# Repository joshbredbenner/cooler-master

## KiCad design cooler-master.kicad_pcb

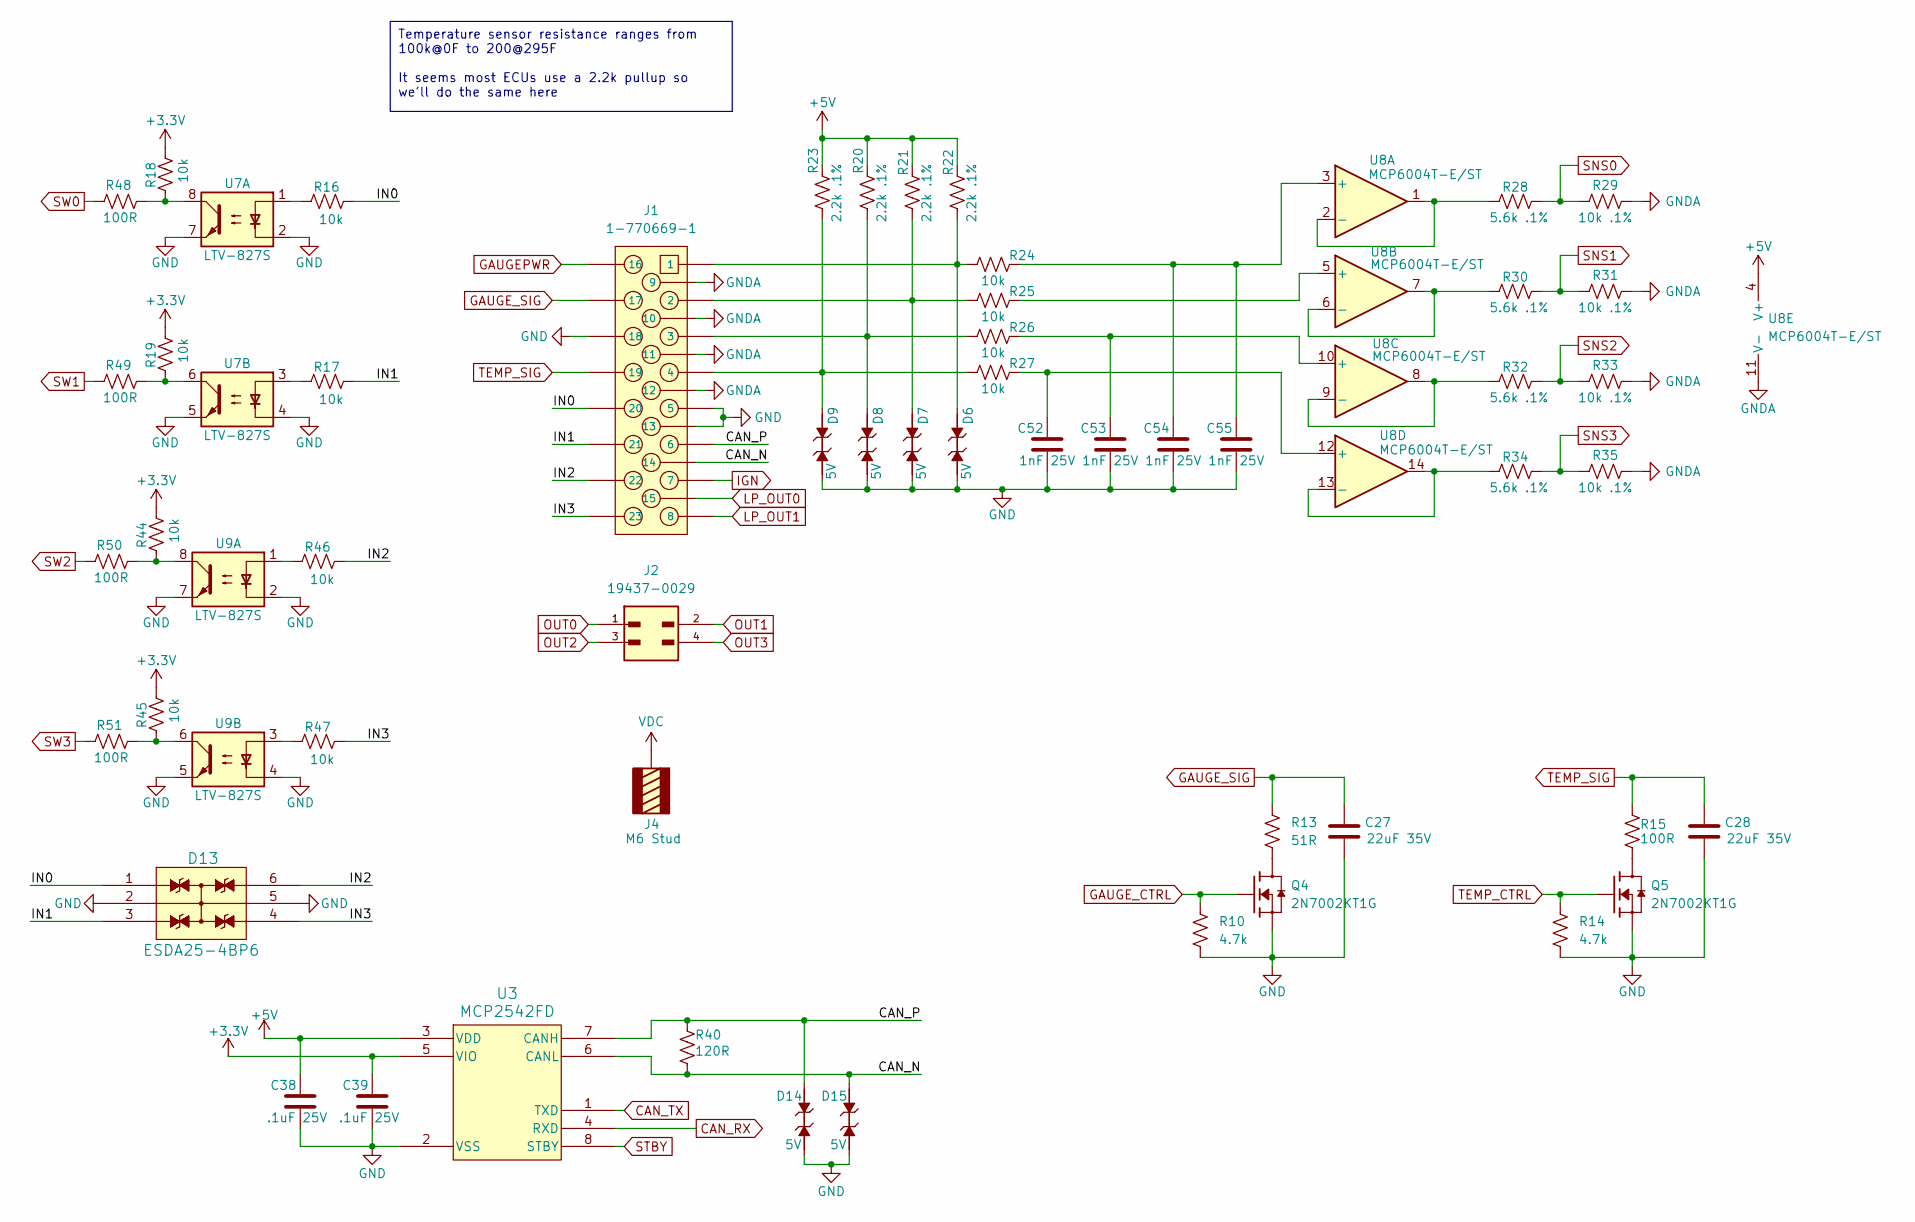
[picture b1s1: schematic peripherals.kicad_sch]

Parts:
C27, C28: 22uF 35V; C_0805_2012Metric
C38, C39: .1uF 25V; C_0402_1005Metric
C52, C53, C54, C55: 1nF 25V; C_0402_1005Metric
D6, D7, D8, D9, D14, D15: 5V; ESD9B5.0ST5G
D13: ESDA25-4BP6; SOT666_ESDA25_STM
J1: 1-770669-1; 17706691
J2: 19437-0029; MOLEX_19437-0029; PARTREV A
J4: M6 Stud; WP-BUCF_7461059
Q4, Q5: 2N7002KT1G; SOT95P230X110-3N
R10, R14: 4.7k; R_0402_1005Metric
R13: 51R; R_0805_2012Metric
R15: 100R; R_0805_2012Metric
R16, R17, R18, R19, R24, R25, R26, R27, R44, R45, R46, R47: 10k; R_0402_1005Metric
R20, R21, R22, R23: 2.2k .1%; R_0402_1005Metric
R28, R30, R32, R34: 5.6k .1%; R_0402_1005Metric
R29, R31, R33, R35: 10k .1%; R_0402_1005Metric
R40: 120R; R_0603_1608Metric
R48, R49, R50, R51: 100R; R_0402_1005Metric
U3: MCP2542FD; SOIC8_4P9X3P9MC_MCH
U7, U9: LTV-827S; SMDIP-8_W9.53mm
U8: MCP6004T-E/ST; SOP65P640X120-14N

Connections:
+3.3V: C39.1, R18.1, R19.1, R44.1, R45.1, U3.5 (VIO); also elsewhere on the board
+5V: C38.1, R20.1, R21.1, R22.1, R23.1, U3.3 (VDD), U8.4 (V+); also elsewhere on the board
/Peripherals/CAN_N: D15.2, J1.14, R40.2, U3.6 (CANL)
/Peripherals/CAN_P: D14.2, J1.6, R40.1, U3.7 (CANH)
/Peripherals/IN0: D13.1, J1.20, R16.1
/Peripherals/IN1: D13.3, J1.21, R17.1
/Peripherals/IN2: D13.6, J1.22, R46.1
/Peripherals/IN3: D13.4, J1.23, R47.1
CAN_RX: U3.4 (RXD); also elsewhere on the board
CAN_TX: U3.1 (TXD); also elsewhere on the board
GAUGEPWR: J1.16; also elsewhere on the board
GAUGE_CTRL: Q4.1 (G), R10.1; also elsewhere on the board
GAUGE_SIG: C27.1, J1.17, R13.1
GND: C27.2, C28.2, C38.2, C39.2, C52.2, C53.2, C54.2, C55.2, D6.2, D7.2, D8.2, D9.2, D13.2, D13.5, D14.1, D15.1, J1.5, J1.13, J1.18, Q4.2 (S), Q5.2 (S), R10.2, R14.2, U3.2 (VSS), U7.2, U7.4, U7.5, U7.7, U9.2, U9.4, U9.5, U9.7; also elsewhere on the board
GNDA: J1.9, J1.10, J1.11, J1.12, R29.2, R31.2, R33.2, R35.2, U8.11 (V-); also elsewhere on the board
IGN: J1.7; also elsewhere on the board
LP_OUT0: J1.15; also elsewhere on the board
LP_OUT1: J1.8; also elsewhere on the board
unnamed: D6.1, J1.1, R22.2, R24.1
unnamed: D7.1, J1.2, R21.2, R25.1
unnamed: D8.1, J1.3, R20.2, R26.1
unnamed: D9.1, J1.4, R23.2, R27.1
unnamed: Q4.3 (D), R13.2
unnamed: Q5.3 (D), R15.2
unnamed: R16.2, U7.1
unnamed: R17.2, U7.3
unnamed: R18.2, R48.2, U7.8
unnamed: R19.2, R49.2, U7.6
unnamed: R44.2, R50.2, U9.8
unnamed: R45.2, R51.2, U9.6
unnamed: R46.2, U9.1
unnamed: R47.2, U9.3
unnamed: C54.1, C55.1, R24.2, U8.3 (+)
unnamed: R28.2, U8.1, U8.2 (-)
unnamed: R25.2, U8.5 (+)
unnamed: R30.2, U8.6 (-), U8.7
unnamed: C53.1, R26.2, U8.10 (+)
unnamed: R32.2, U8.8, U8.9 (-)
unnamed: C52.1, R27.2, U8.12 (+)
unnamed: R34.2, U8.13 (-), U8.14
OUT0: J2.1; also elsewhere on the board
OUT1: J2.2; also elsewhere on the board
OUT2: J2.3; also elsewhere on the board
OUT3: J2.4; also elsewhere on the board
SNS0: R28.1, R29.1; also elsewhere on the board
SNS1: R30.1, R31.1; also elsewhere on the board
SNS2: R32.1, R33.1; also elsewhere on the board
SNS3: R34.1, R35.1; also elsewhere on the board
STBY: U3.8 (STBY); also elsewhere on the board
SW0: R48.1
SW1: R49.1
SW2: R50.1
SW3: R51.1
TEMP_CTRL: Q5.1 (G), R14.1; also elsewhere on the board
TEMP_SIG: C28.1, J1.19, R15.1
VDC: J4.1; also elsewhere on the board

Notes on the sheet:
Temperature sensor resistance ranges from 100k@0F to 200@295F It seems most ECUs use a 2.2k pullup so we'll do the same here

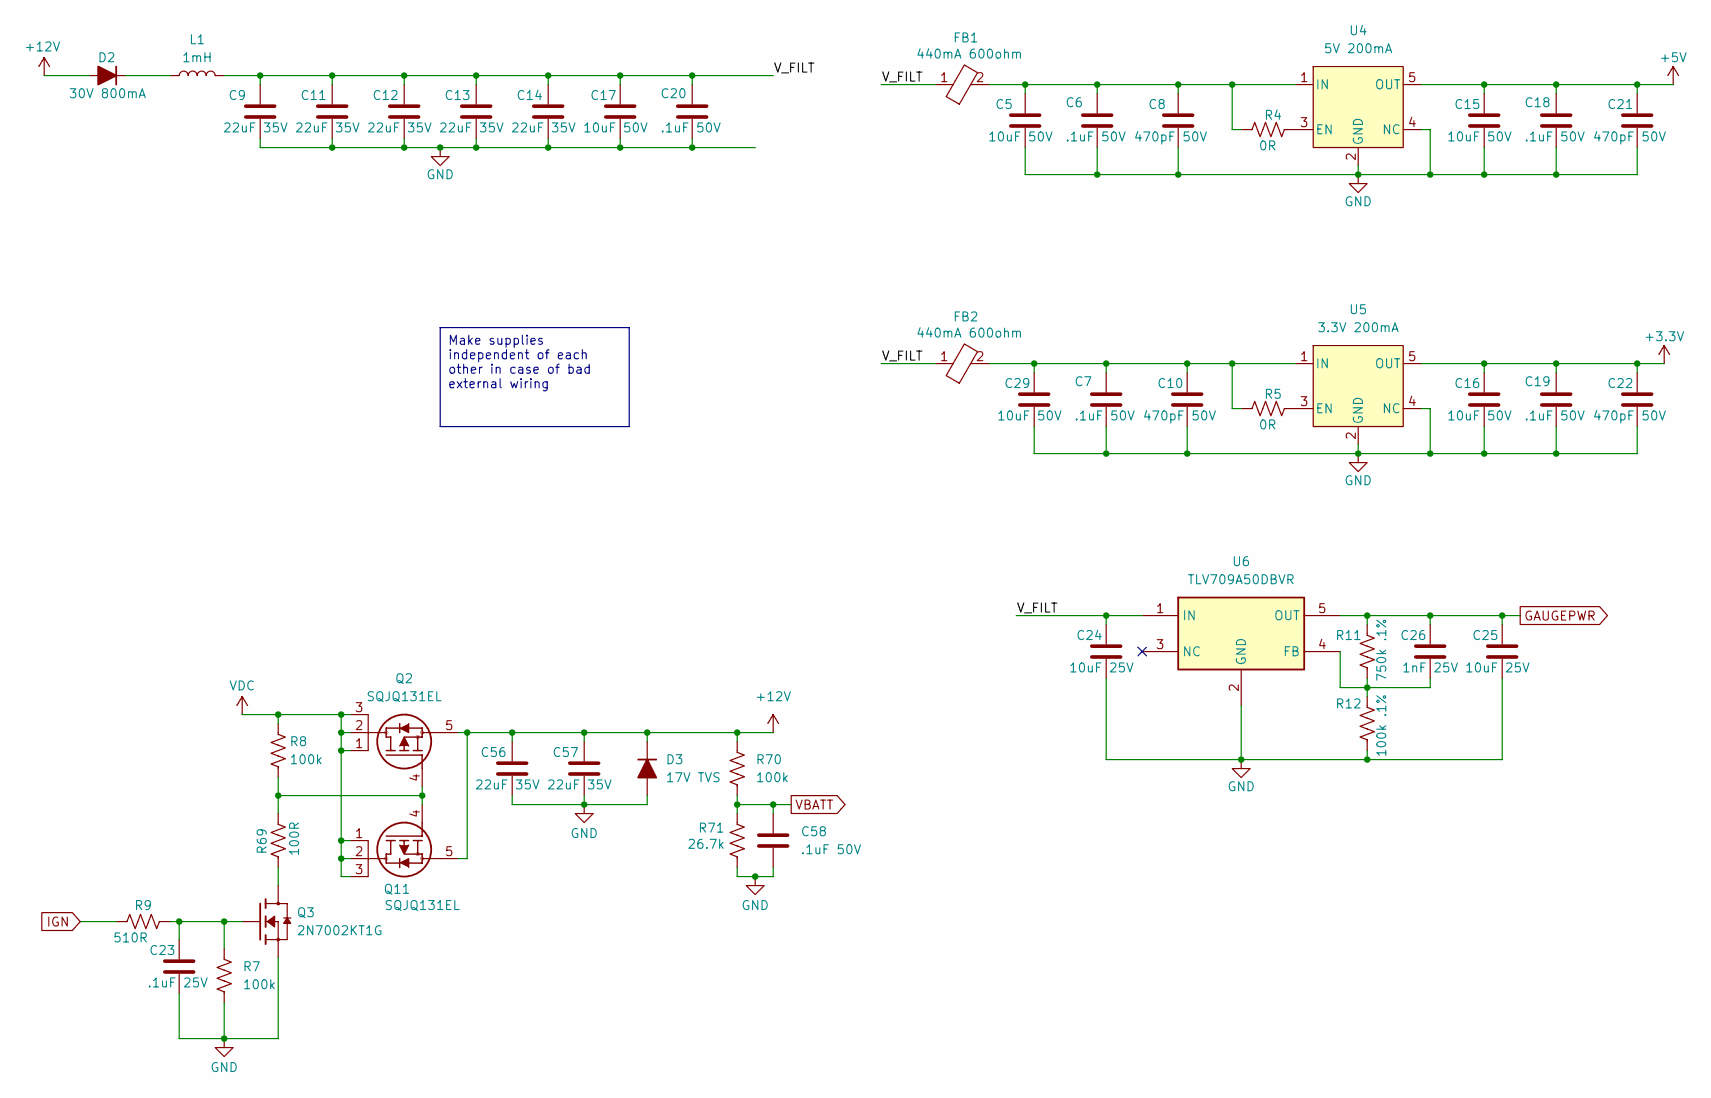
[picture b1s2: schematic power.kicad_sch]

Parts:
C5, C15, C16, C17, C29: 10uF 50V; C_0805_2012Metric
C6, C7, C18, C19, C20: .1uF 50V; C_0603_1608Metric
C8, C10, C21, C22: 470pF 50V; C_0402_1005Metric
C9, C11, C12, C13, C14, C56, C57: 22uF 35V; C_0805_2012Metric
C23: .1uF 25V; C_0402_1005Metric
C24, C25: 10uF 25V; C_0805_2012Metric
C26: 1nF 25V; C_0402_1005Metric
C58: .1uF 50V; C_0402_1005Metric
D2: 30V 800mA; SC-76, SOD-323
D3: 17V TVS; SOD123W
FB1, FB2: 440mA 600ohm; R_0402_1005Metric
L1: 1mH; DR73-102-R
Q2, Q11: SQJQ131EL; TO_EL-T1_GE3_VIS
Q3: 2N7002KT1G; SOT95P230X110-3N
R4, R5: 0R; R_0402_1005Metric
R7, R8, R70: 100k; R_0402_1005Metric
R9: 510R; R_0402_1005Metric
R11: 750k .1%; R_0402_1005Metric
R12: 100k .1%; R_0402_1005Metric
R69: 100R; R_0402_1005Metric
R71: 26.7k; R_0402_1005Metric
U4: 5V 200mA; SC-74A, SOT-753
U5: 3.3V 200mA; SC-74A, SOT-753
U6: TLV709A50DBVR; SOT95P280X145-5N

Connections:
+3.3V: C16.1, C19.1, C22.1, U5.5 (OUT); also elsewhere on the board
+5V: C15.1, C18.1, C21.1, U4.5 (OUT); also elsewhere on the board
+12V: C56.1, C57.1, D2.2, D3.1 (K), Q2.5, Q11.5, R70.1; also elsewhere on the board
/Power/V_FILT: C9.1, C11.1, C12.1, C13.1, C14.1, C17.1, C20.1, C24.1, FB1.1, FB2.1, L1.2, U6.1 (IN)
GAUGEPWR: C25.1, C26.1, R11.1, U6.5 (OUT); also elsewhere on the board
GND: C5.2, C6.2, C7.2, C8.2, C9.2, C10.2, C11.2, C12.2, C13.2, C14.2, C15.2, C16.2, C17.2, C18.2, C19.2, C20.2, C21.2, C22.2, C23.2, C24.2, C25.2, C29.2, C56.2, C57.2, C58.2, D3.2 (A), Q3.2 (S), R7.2, R12.2, R71.2, U4.2 (GND), U4.4 (NC), U5.2 (GND), U5.4 (NC), U6.2 (GND); also elsewhere on the board
IGN: R9.1; also elsewhere on the board
unnamed: D2.1, L1.1
unnamed: Q3.3 (D), R69.2
unnamed: C23.1, Q3.1 (G), R7.1, R9.2
unnamed: Q2.4, Q11.4, R8.2, R69.1
unnamed: R4.2, U4.3 (EN)
unnamed: C5.1, C6.1, C8.1, FB1.2, R4.1, U4.1 (IN)
unnamed: R5.2, U5.3 (EN)
unnamed: C7.1, C10.1, C29.1, FB2.2, R5.1, U5.1 (IN)
unnamed: C26.2, R11.2, R12.1, U6.4 (FB)
VBATT: C58.1, R70.2, R71.1; also elsewhere on the board
VDC: Q2.1, Q2.2, Q2.3, Q11.1, Q11.2, Q11.3, R8.1; also elsewhere on the board

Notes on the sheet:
Make supplies independent of each other in case of bad external wiring

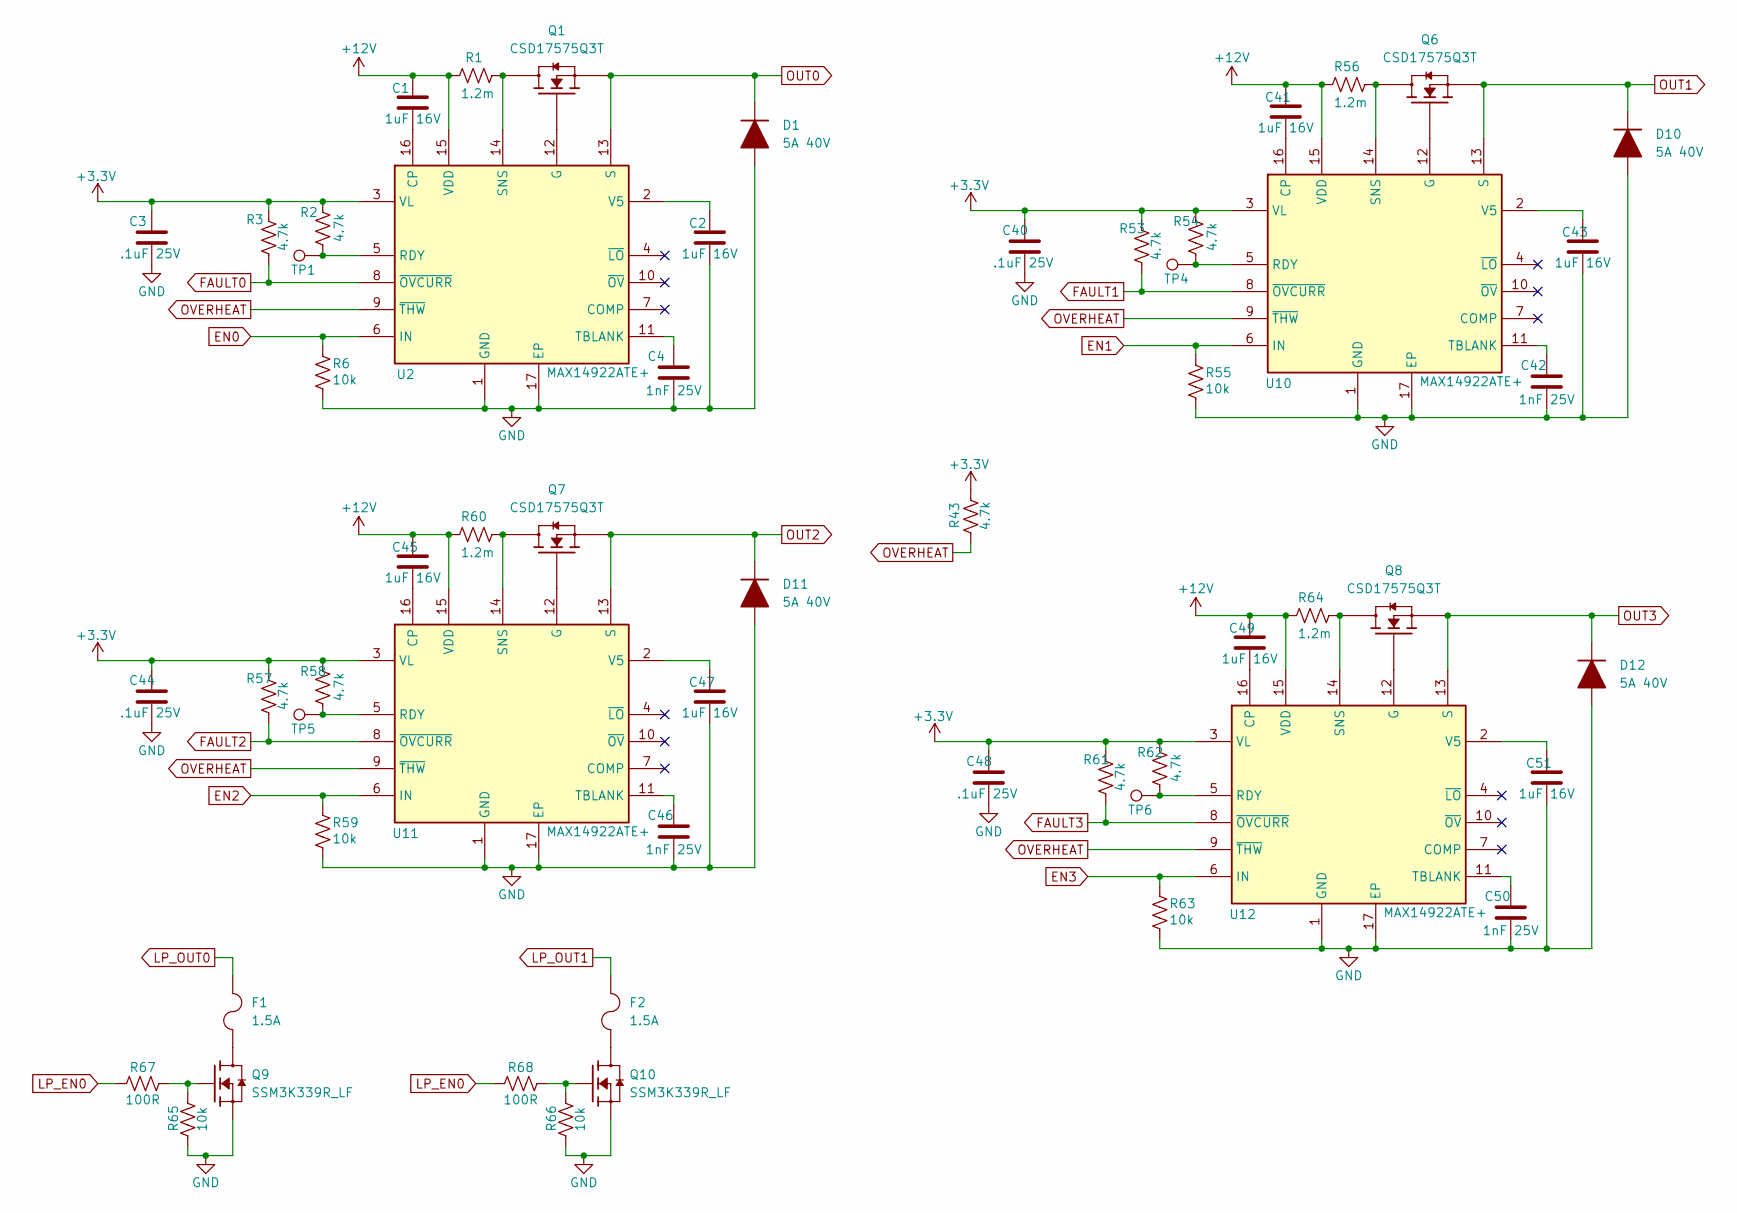
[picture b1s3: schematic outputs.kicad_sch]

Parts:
C1, C2, C41, C43, C45, C47, C49, C51: 1uF 16V; C_0402_1005Metric
C3, C40, C44, C48: .1uF 25V; C_0402_1005Metric
C4, C42, C46, C50: 1nF 25V; C_0402_1005Metric
D1, D10, D11, D12: 5A 40V; DO-214AC
F1, F2: 1.5A; FUSC1608X56N
Q1, Q6, Q7, Q8: CSD17575Q3T; TRANS_CSD17308Q3
Q9, Q10: SSM3K339R_LF; SOT-23F_TOS
R1, R56, R60, R64: 1.2m; R_2512_6332Metric_Pad1.40x3.35mm_HandSolder
R2, R3, R43, R53, R54, R57, R58, R61, R62: 4.7k; R_0402_1005Metric
R6, R55, R59, R63, R65, R66: 10k; R_0402_1005Metric
R67, R68: 100R; R_0402_1005Metric
TP1, TP4, TP5, TP6: TestPoint; TestPoint_Pad_D1.0mm
U2, U10, U11, U12: MAX14922ATE+; QFN50P300X300X80-17N

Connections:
+3.3V: C3.1, C40.1, C44.1, C48.1, R2.1, R3.1, R43.1, R53.1, R54.1, R57.1, R58.1, R61.1, R62.1, U2.3 (VL), U10.3 (VL), U11.3 (VL), U12.3 (VL); also elsewhere on the board
+12V: C1.1, C41.1, C45.1, C49.1, R1.1, R56.1, R60.1, R64.1, U2.15 (VDD), U10.15 (VDD), U11.15 (VDD), U12.15 (VDD); also elsewhere on the board
EN0: R6.1, U2.6 (IN); also elsewhere on the board
EN1: R55.1, U10.6 (IN); also elsewhere on the board
EN2: R59.1, U11.6 (IN); also elsewhere on the board
EN3: R63.1, U12.6 (IN); also elsewhere on the board
FAULT0: R3.2, U2.8 (~OVCURR); also elsewhere on the board
FAULT1: R53.2, U10.8 (~OVCURR); also elsewhere on the board
FAULT2: R57.2, U11.8 (~OVCURR); also elsewhere on the board
FAULT3: R61.2, U12.8 (~OVCURR); also elsewhere on the board
GND: C2.2, C3.2, C4.2, C40.2, C42.2, C43.2, C44.2, C46.2, C47.2, C48.2, C50.2, C51.2, D1.2 (A), D10.2 (A), D11.2 (A), D12.2 (A), Q9.2, Q10.2, R6.2, R55.2, R59.2, R63.2, R65.2, R66.2, U2.1 (GND), U2.17 (EP), U10.1 (GND), U10.17 (EP), U11.1 (GND), U11.17 (EP), U12.1 (GND), U12.17 (EP); also elsewhere on the board
LP_EN0: R67.1, R68.1; also elsewhere on the board
LP_OUT0: F1.2; also elsewhere on the board
LP_OUT1: F2.2; also elsewhere on the board
unnamed: F1.1, Q9.3
unnamed: F2.1, Q10.3
unnamed: Q1.4 (G), U2.12 (G)
unnamed: Q6.4 (G), U10.12 (G)
unnamed: Q7.4 (G), U11.12 (G)
unnamed: Q8.4 (G), U12.12 (G)
unnamed: Q9.1, R65.1, R67.2
unnamed: Q10.1, R66.1, R68.2
unnamed: C1.2, U2.16 (CP)
unnamed: R2.2, TP1.1, U2.5 (RDY)
unnamed: Q1.5 (D), Q1.6 (D), Q1.7 (D), Q1.8 (D), Q1.9 (D), R1.2, U2.14 (SNS)
unnamed: C4.1, U2.11 (TBLANK)
unnamed: C2.1, U2.2 (V5)
unnamed: C41.2, U10.16 (CP)
unnamed: R54.2, TP4.1, U10.5 (RDY)
unnamed: Q6.5 (D), Q6.6 (D), Q6.7 (D), Q6.8 (D), Q6.9 (D), R56.2, U10.14 (SNS)
unnamed: C42.1, U10.11 (TBLANK)
unnamed: C43.1, U10.2 (V5)
unnamed: C45.2, U11.16 (CP)
unnamed: R58.2, TP5.1, U11.5 (RDY)
unnamed: Q7.5 (D), Q7.6 (D), Q7.7 (D), Q7.8 (D), Q7.9 (D), R60.2, U11.14 (SNS)
unnamed: C46.1, U11.11 (TBLANK)
unnamed: C47.1, U11.2 (V5)
unnamed: C49.2, U12.16 (CP)
unnamed: R62.2, TP6.1, U12.5 (RDY)
unnamed: Q8.5 (D), Q8.6 (D), Q8.7 (D), Q8.8 (D), Q8.9 (D), R64.2, U12.14 (SNS)
unnamed: C50.1, U12.11 (TBLANK)
unnamed: C51.1, U12.2 (V5)
OUT0: D1.1 (K), Q1.1 (S), Q1.2 (S), Q1.3 (S), U2.13 (S); also elsewhere on the board
OUT1: D10.1 (K), Q6.1 (S), Q6.2 (S), Q6.3 (S), U10.13 (S); also elsewhere on the board
OUT2: D11.1 (K), Q7.1 (S), Q7.2 (S), Q7.3 (S), U11.13 (S); also elsewhere on the board
OUT3: D12.1 (K), Q8.1 (S), Q8.2 (S), Q8.3 (S), U12.13 (S); also elsewhere on the board
OVERHEAT: R43.2, U2.9 (~THW), U10.9 (~THW), U11.9 (~THW), U12.9 (~THW); also elsewhere on the board

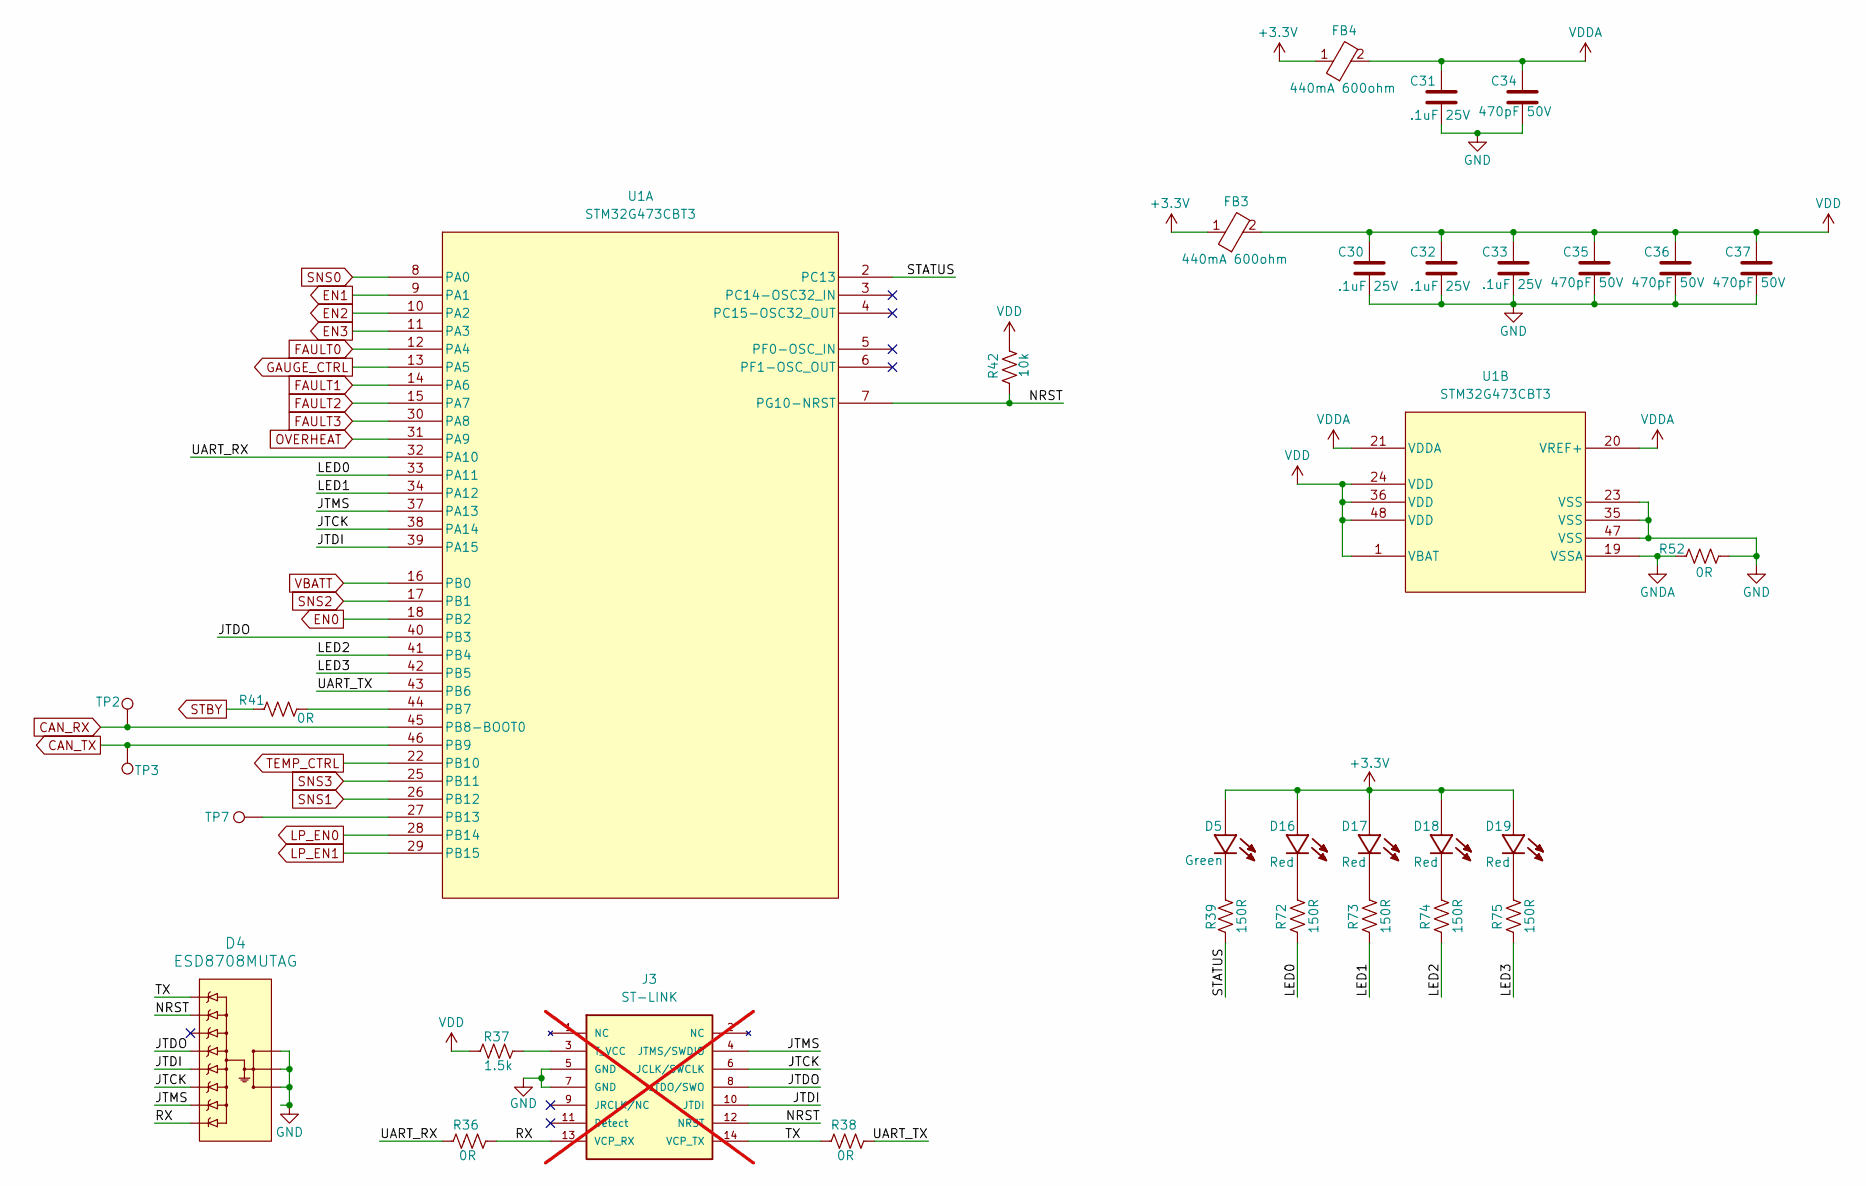
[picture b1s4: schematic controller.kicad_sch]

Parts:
C30, C31, C32, C33: .1uF 25V; C_0402_1005Metric
C34, C35, C36, C37: 470pF 50V; C_0402_1005Metric
D4: ESD8708MUTAG; UDFN14_517CN_ONS
D5: Green; LED_SML-D12V1WT86
D16, D17, D18, D19: Red; LED_SML-D12V1WT86
FB3, FB4: 440mA 600ohm; R_0402_1005Metric
J3: ST-LINK; SAMTEC_FTSH-107-01-F-DV-K-P; not fitted
R36, R38, R41, R52: 0R; R_0402_1005Metric
R37: 1.5k; R_0603_1608Metric
R39, R72, R73, R74, R75: 150R; R_0603_1608Metric
R42: 10k; R_0402_1005Metric
TP2, TP3, TP7: TestPoint; TestPoint_Pad_D1.0mm
U1: STM32G473CBT3; LQFP48-7x7mm

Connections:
+3.3V: D5.A, D16.A, D17.A, D18.A, D19.A, FB3.1, FB4.1; also elsewhere on the board
/Controller/JTCK: D4.8, J3.6 (JCLK/SWCLK), U1.38 (PA14)
/Controller/JTDI: D4.7, J3.10 (JTDI), U1.39 (PA15)
/Controller/JTDO: D4.5, J3.8 (JTDO/SWO), U1.40 (PB3)
/Controller/JTMS: D4.10, J3.4 (JTMS/SWDIO), U1.37 (PA13)
/Controller/LED0: R72.2, U1.33 (PA11)
/Controller/LED1: R73.2, U1.34 (PA12)
/Controller/LED2: R74.2, U1.41 (PB4)
/Controller/LED3: R75.2, U1.42 (PB5)
/Controller/NRST: D4.2, J3.12 (NRST), R42.2, U1.7 (PG10-NRST)
/Controller/RX: D4.11, J3.13 (VCP_RX), R36.2
/Controller/STATUS: R39.2, U1.2 (PC13)
/Controller/TX: D4.1, J3.14 (VCP_TX), R38.1
/Controller/UART_RX: R36.1, U1.32 (PA10)
/Controller/UART_TX: R38.2, U1.43 (PB6)
CAN_RX: TP2.1, U1.45 (PB8-BOOT0); also elsewhere on the board
CAN_TX: TP3.1, U1.46 (PB9); also elsewhere on the board
EN0: U1.18 (PB2); also elsewhere on the board
EN1: U1.9 (PA1); also elsewhere on the board
EN2: U1.10 (PA2); also elsewhere on the board
EN3: U1.11 (PA3); also elsewhere on the board
FAULT0: U1.12 (PA4); also elsewhere on the board
FAULT1: U1.14 (PA6); also elsewhere on the board
FAULT2: U1.15 (PA7); also elsewhere on the board
FAULT3: U1.30 (PA8); also elsewhere on the board
GAUGE_CTRL: U1.13 (PA5); also elsewhere on the board
GND: C30.2, C31.2, C32.2, C33.2, C34.2, C35.2, C36.2, C37.2, D4.3, D4.6, D4.9, J3.5 (GND), J3.7 (GND), R52.2, U1.23 (VSS), U1.35 (VSS), U1.47 (VSS); also elsewhere on the board
GNDA: R52.1, U1.19 (VSSA); also elsewhere on the board
LP_EN0: U1.28 (PB14); also elsewhere on the board
LP_EN1: U1.29 (PB15)
unnamed: D5.C, R39.1
unnamed: D16.C, R72.1
unnamed: D17.C, R73.1
unnamed: D18.C, R74.1
unnamed: D19.C, R75.1
unnamed: J3.3 (T_VCC), R37.1
unnamed: R41.2, U1.44 (PB7)
unnamed: TP7.1, U1.27 (PB13)
OVERHEAT: U1.31 (PA9); also elsewhere on the board
SNS0: U1.8 (PA0); also elsewhere on the board
SNS1: U1.26 (PB12); also elsewhere on the board
SNS2: U1.17 (PB1); also elsewhere on the board
SNS3: U1.25 (PB11); also elsewhere on the board
STBY: R41.1; also elsewhere on the board
TEMP_CTRL: U1.22 (PB10); also elsewhere on the board
VBATT: U1.16 (PB0); also elsewhere on the board
VDD: C30.1, C32.1, C33.1, C35.1, C36.1, C37.1, FB3.2, R37.2, R42.1, U1.1 (VBAT), U1.24 (VDD), U1.36 (VDD), U1.48 (VDD)
VDDA: C31.1, C34.1, FB4.2, U1.20 (VREF+), U1.21 (VDDA)

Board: 4 copper layers, 193 parts (0 on the bottom side), 126 nets, no tracks yet.

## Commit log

2024-09-22 Adding Kicad files
2024-09-22 More sheets and switching to external FET HSS
2024-09-23 Added power domain stuff
2024-10-02 Added peripherals page and started gauge control
2024-10-02 Add kicad lib as submodule and update path
2024-10-02 Finished gauge power circuit
2024-10-03 Change gauge LDO
2024-10-11 Added opto-isolated input switches and some sensor stuff
2024-11-13 Some perpipheral changes?
2024-11-13 New footprints
2024-11-14 Have footprint library track master and use local library
2025-01-04 Small changes to schematic
2025-02-01 Initial schematic is done
